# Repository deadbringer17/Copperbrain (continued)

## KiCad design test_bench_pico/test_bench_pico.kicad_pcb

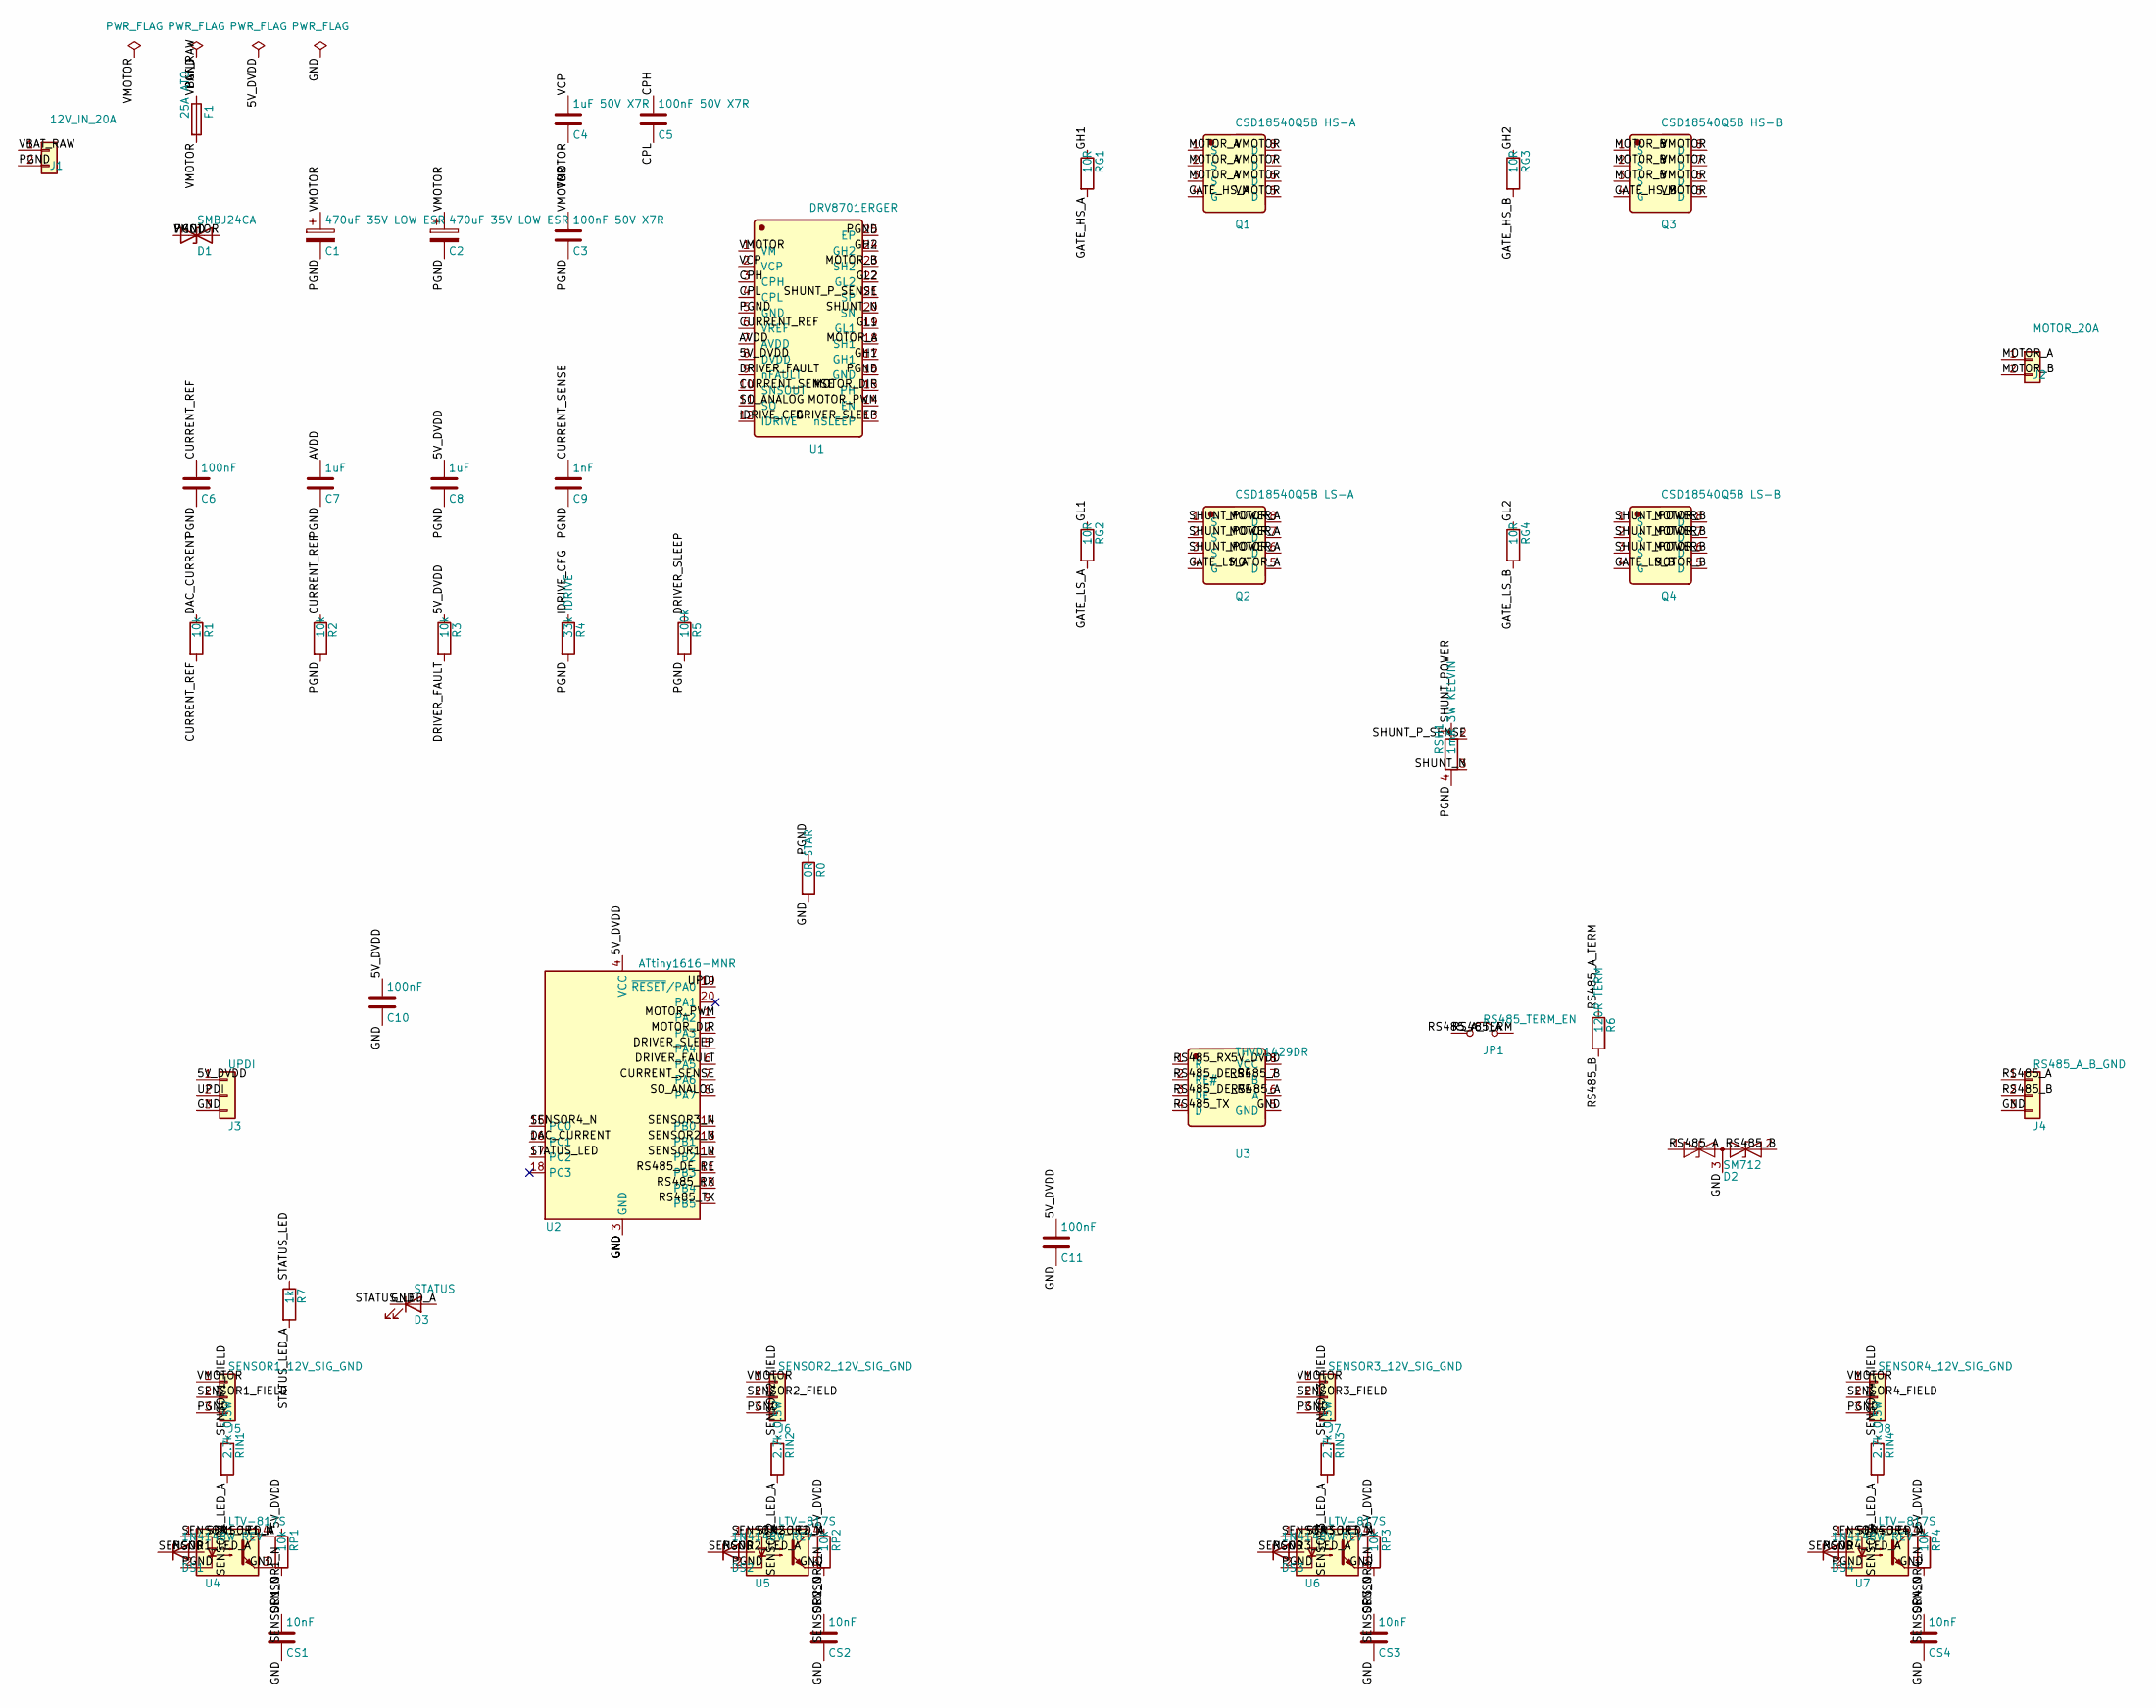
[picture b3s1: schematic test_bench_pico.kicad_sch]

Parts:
C1, C2: 470uF 35V LOW ESR; CP_Radial_D12.5mm_P5.00mm
C3, C5: 100nF 50V X7R; C_0805_2012Metric
C4: 1uF 50V X7R; C_0805_2012Metric
C6, C10, C11: 100nF; C_0603_1608Metric
C7, C8: 1uF; C_0603_1608Metric
C9: 1nF; C_0603_1608Metric
CS1, CS2, CS3, CS4: 10nF; C_0603_1608Metric
D1: SMBJ24CA; D_SMB
D2: SM712; SOT-23
D3: STATUS; LED_0603_1608Metric
DS1, DS2, DS3, DS4: 1N4148W REV; D_SOD-123
F1: 25A ATO; Fuse_Blade_ATO_directSolder
J1: 12V_IN_20A; Wuerth_691311400102_P7.62mm
J2: MOTOR_20A; Wuerth_691311400102_P7.62mm
J3: UPDI; PinHeader_1x03_P2.54mm_Vertical
J4: RS485_A_B_GND; TerminalBlock_4Ucon_1x03_P3.50mm_Vertical
J5: SENSOR1_12V_SIG_GND; TerminalBlock_4Ucon_1x03_P3.50mm_Vertical
J6: SENSOR2_12V_SIG_GND; TerminalBlock_4Ucon_1x03_P3.50mm_Vertical
J7: SENSOR3_12V_SIG_GND; TerminalBlock_4Ucon_1x03_P3.50mm_Vertical
J8: SENSOR4_12V_SIG_GND; TerminalBlock_4Ucon_1x03_P3.50mm_Vertical
JP1: RS485_TERM_EN; SolderJumper-2_P1.3mm_Open_Pad1.0x1.5mm
Q1: CSD18540Q5B HS-A; CSD18540Q5B; MPN CSD18540Q5B; LCSC C86513
Q2: CSD18540Q5B LS-A; CSD18540Q5B; MPN CSD18540Q5B; LCSC C86513
Q3: CSD18540Q5B HS-B; CSD18540Q5B; MPN CSD18540Q5B; LCSC C86513
Q4: CSD18540Q5B LS-B; CSD18540Q5B; MPN CSD18540Q5B; LCSC C86513
R0: 0R STAR; R_0805_2012Metric
R1, R2, R3: 10k; R_0603_1608Metric
R4: 33k IDRIVE; R_0603_1608Metric
R5: 100k; R_0603_1608Metric
R6: 120R TERM; R_0805_2012Metric
R7: 1k; R_0603_1608Metric
RG1, RG2, RG3, RG4: 10R; R_0805_2012Metric
RIN1, RIN2, RIN3, RIN4: 2.7k 0.5W; R_2010_5025Metric
RP1, RP2, RP3, RP4: 10k; R_0603_1608Metric
RSH1: 1mR 3W KELVIN; R_Shunt_Vishay_WSK2512_6332Metric_T2.21mm
U1: DRV8701ERGER; MPN DRV8701ERGER; LCSC C90964
U2: ATtiny1616-MNR; VQFN-20-1EP_3x3mm_P0.45mm_EP1.55x1.55mm; MPN ATTINY1616-MNR; LCSC C507118
U3: THVD1429DR; MPN THVD1429DR; LCSC C1850236
U4, U5, U6, U7: LTV-817S; SOP-4_7.5x4.1mm_P2.54mm

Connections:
/5V_DVDD: C8.1, C10.1, C11.1, J3.1, R3.1, RP1.1, RP2.1, RP3.1, RP4.1, U1.8 (DVDD), U2.4 (VCC), U3.8 (VCC)
/AVDD: C7.1, U1.7 (AVDD)
/CPH: C5.1, U1.3 (CPH)
/CPL: C5.2, U1.4 (CPL)
/CURRENT_REF: C6.1, R1.2, R2.1, U1.6 (VREF)
/CURRENT_SENSE: C9.1, U1.10 (SNSOUT), U2.7 (PA6)
/DAC_CURRENT: R1.1, U2.16 (PC1)
/DRIVER_FAULT: R3.2, U1.9 (nFAULT), U2.6 (PA5)
/DRIVER_SLEEP: R5.1, U1.13 (nSLEEP), U2.5 (PA4)
/GATE_HS_A: Q1.4 (G), RG1.2
/GATE_HS_B: Q3.4 (G), RG3.2
/GATE_LS_A: Q2.4 (G), RG2.2
/GATE_LS_B: Q4.4 (G), RG4.2
/GH1: RG1.1, U1.17 (GH1)
/GH2: RG3.1, U1.24 (GH2)
/GL1: RG2.1, U1.19 (GL1)
/GL2: RG4.1, U1.22 (GL2)
/GND: C10.2, C11.2, CS1.2, CS2.2, CS3.2, CS4.2, D2.3 (common), D3.1 (K), J3.3, J4.3, R0.2, U2.3 (GND), U2.21 (GND), U3.5 (GND), U4.3, U5.3, U6.3, U7.3
/IDRIVE_CFG: R4.1, U1.12 (IDRIVE)
/MOTOR_A: J2.1, Q1.1 (S), Q1.2 (S), Q1.3 (S), Q2.5 (D), Q2.6 (D), Q2.7 (D), Q2.8 (D), U1.18 (SH1)
/MOTOR_B: J2.2, Q3.1 (S), Q3.2 (S), Q3.3 (S), Q4.5 (D), Q4.6 (D), Q4.7 (D), Q4.8 (D), U1.23 (SH2)
/MOTOR_DIR: U1.15 (PH), U2.2 (PA3)
/MOTOR_PWM: U1.14 (EN), U2.1 (PA2)
/PGND: C1.2, C2.2, C3.2, C6.2, C7.2, C8.2, C9.2, D1.1 (A1), DS1.2 (A), DS2.2 (A), DS3.2 (A), DS4.2 (A), J1.2, J5.3, J6.3, J7.3, J8.3, R0.1, R2.2, R4.2, R5.2, RSH1.4, U1.5 (GND), U1.16 (GND), U1.25 (EP), U4.2, U5.2, U6.2, U7.2
/RS485_A: D2.1 (A1), J4.1, JP1.1 (A), U3.6 (A)
/RS485_A_TERM: JP1.2 (B), R6.1
/RS485_B: D2.2 (A2), J4.2, R6.2, U3.7 (B)
/RS485_DE_RE: U2.11 (PB3), U3.2 (RE#), U3.3 (DE)
/RS485_RX: U2.10 (PB4), U3.1 (R)
/RS485_TX: U2.9 (PB5), U3.4 (D)
/SENSOR1_FIELD: J5.2, RIN1.1
/SENSOR1_LED_A: DS1.1 (K), RIN1.2, U4.1
/SENSOR1_N: CS1.1, RP1.2, U2.12 (PB2), U4.4
/SENSOR2_FIELD: J6.2, RIN2.1
/SENSOR2_LED_A: DS2.1 (K), RIN2.2, U5.1
/SENSOR2_N: CS2.1, RP2.2, U2.13 (PB1), U5.4
/SENSOR3_FIELD: J7.2, RIN3.1
/SENSOR3_LED_A: DS3.1 (K), RIN3.2, U6.1
/SENSOR3_N: CS3.1, RP3.2, U2.14 (PB0), U6.4
/SENSOR4_FIELD: J8.2, RIN4.1
/SENSOR4_LED_A: DS4.1 (K), RIN4.2, U7.1
/SENSOR4_N: CS4.1, RP4.2, U2.15 (PC0), U7.4
/SHUNT_N: RSH1.3, U1.20 (SN)
/SHUNT_POWER: Q2.1 (S), Q2.2 (S), Q2.3 (S), Q4.1 (S), Q4.2 (S), Q4.3 (S), RSH1.1
/SHUNT_P_SENSE: RSH1.2, U1.21 (SP)
/SO_ANALOG: U1.11 (SO), U2.8 (PA7)
/STATUS_LED: R7.1, U2.17 (PC2)
/STATUS_LED_A: D3.2 (A), R7.2
/UPDI: J3.2, U2.19 (~RESET/PA0)
/VBAT_RAW: F1.1, J1.1
/VCP: C4.1, U1.2 (VCP)
/VMOTOR: C1.1, C2.1, C3.1, C4.2, D1.2 (A2), F1.2, J5.1, J6.1, J7.1, J8.1, Q1.5 (D), Q1.6 (D), Q1.7 (D), Q1.8 (D), Q3.5 (D), Q3.6 (D), Q3.7 (D), Q3.8 (D), U1.1 (VM)

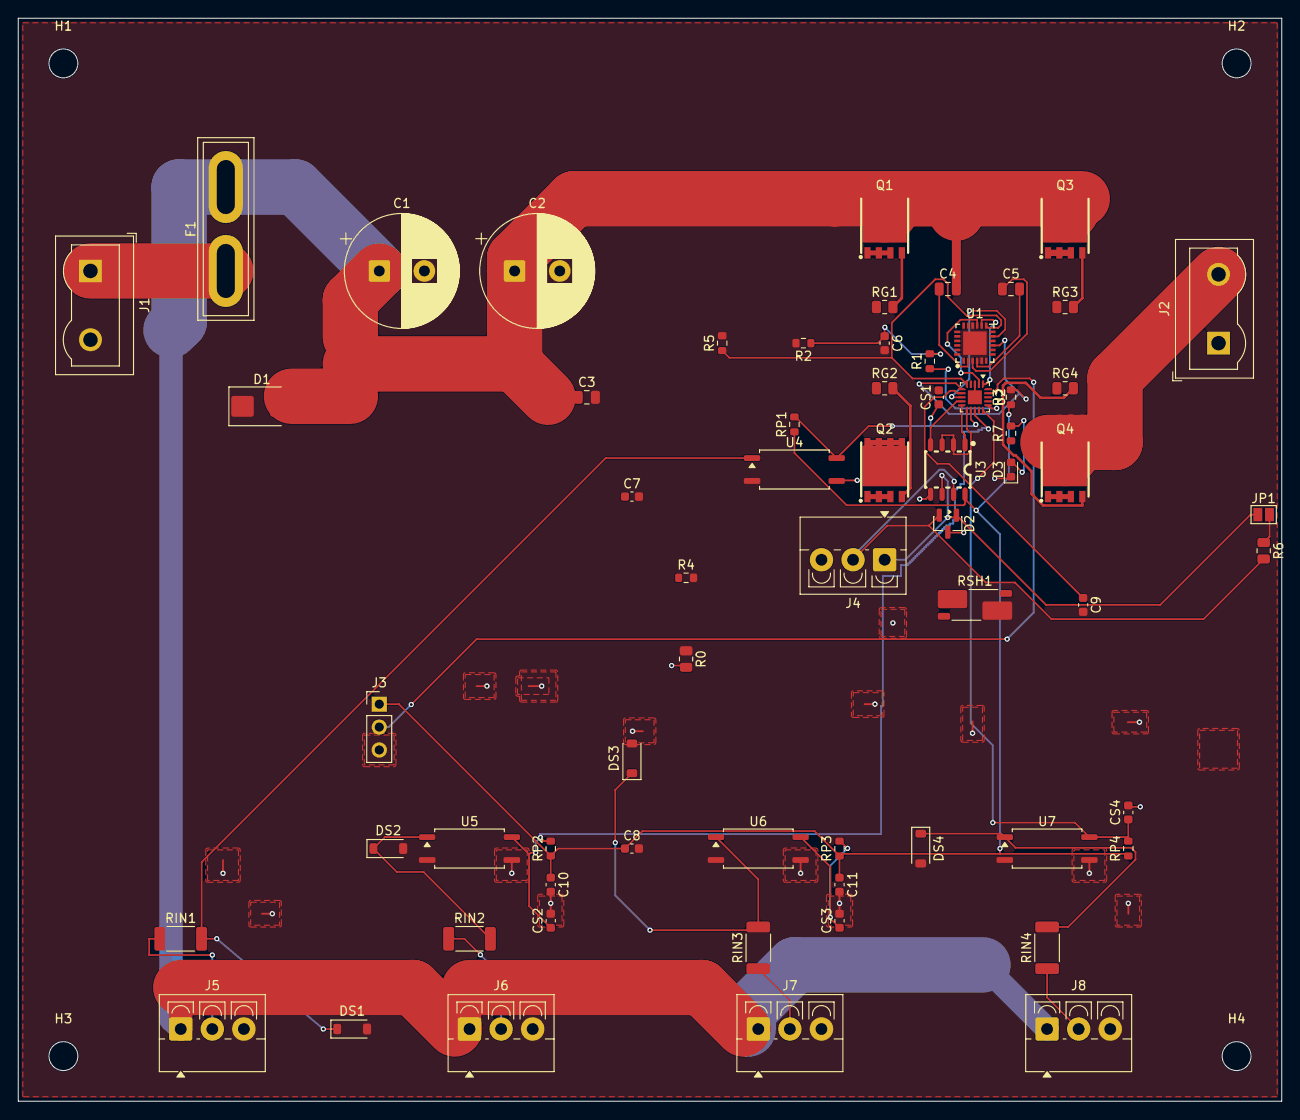
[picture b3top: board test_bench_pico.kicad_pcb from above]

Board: 2 copper layers, 140.0 x 120.0 mm, 68 parts (0 on the bottom side), 52 nets.

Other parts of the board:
H1, H2, H3, H4: MountingHole_3.2mm_M3

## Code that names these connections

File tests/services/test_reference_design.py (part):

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    labels = {str(item.parameters.get("text")) for item in operations if item.kind == "label"}

    assert {"U1", "Q1", "L1", "D1", "RS1", "J1", "J2", "F1", "F2"} <= added
    assert {"VIN_RAW", "VIN_PROTECTED", "SW", "VOUT_PRE_FUSE", "VOUT48", "GND"} <= labels
    assert sum(item.kind == "relayout_pin_label" for item in operations) == sum(
        item.kind == "label" for item in operations
    )
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
    assert {"U1", "U2", "U3", "Q1", "Q2", "Q3", "Q4", "RSH1", "R0"} <= added
    assert {"J5", "J6", "J7", "J8", "U4", "U5", "U6", "U7"} <= added
    assert {"MOTOR_A", "MOTOR_B", "SHUNT_POWER", "RS485_A", "RS485_B"} <= labels
    assert {f"SENSOR{index}_N" for index in range(1, 5)} <= labels
    assert "5V_DVDD" in labels
    assert "PGND" in labels
    assert "3V3" not in labels
    assert any(
        item.kind == "set_paper_size" and item.parameters.get("paper") == "A3"
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    sensor_diode_nets = {
        item.target: item.parameters.get("text")
        for item in operations
        if item.kind == "label" and item.target.startswith("SENSOR1_LED_A:DS1")
    }
    assert sensor_diode_nets == {"SENSOR1_LED_A:DS1.1": "SENSOR1_LED_A"}
    assert any(item.target == "PGND:DS1.2" for item in operations)
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    readability = bldc_schematic_readability_operations(driver)

    assert {"U1", "J1", "J2", "J3", "J4", "F1", "D1"} <= added
    assert {"PHASE_A", "PHASE_B", "PHASE_C", "VM", "GND", "AVDD"} <= labels
    assert {"PWM_AH", "PWM_AL", "PWM_BH", "PWM_BL", "PWM_CH", "PWM_CL"} <= labels
    assert {"SPI_SCLK", "SPI_MOSI", "SPI_MISO", "SPI_CS_N", "FAULT_N"} <= labels
    assert {"ISENSE_A", "ISENSE_B", "ISENSE_C", "HALL_A", "HALL_B", "HALL_C"} <= labels
    assert sum(item.kind == "relayout_pin_label" for item in operations) == 99
    assert sum(item.kind == "move_component" for item in readability) == 28
    assert sum(item.kind == "relayout_pin_label" for item in readability) == 99
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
